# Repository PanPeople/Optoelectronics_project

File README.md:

# Optoelectronic Project

## Group Members:

* Mikołaj Czerniak
* Damian Kociołek
* Michał Stanisławski

## Useful links:

* https://www.electronics-lab.com/project/constant-current-laser-diode-driver-circuit-using-opa2350-opamp/
* https://www.electronics-lab.com/project/adjustable-constant-current-laser-diode-led-driver/
* https://github.com/marcoreps/laser_driver

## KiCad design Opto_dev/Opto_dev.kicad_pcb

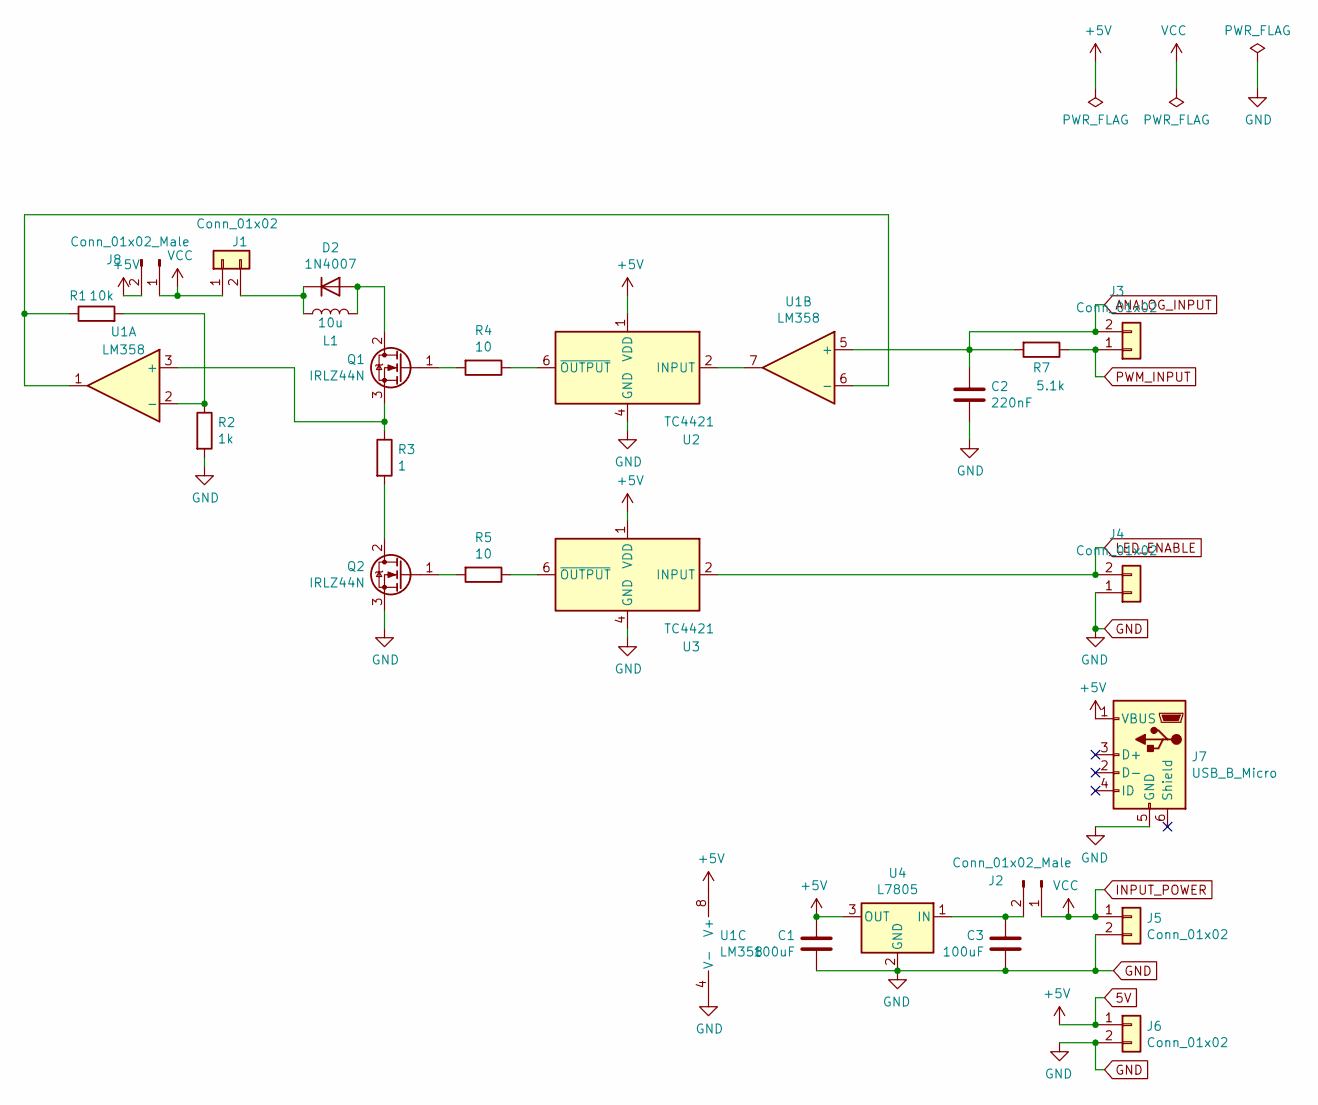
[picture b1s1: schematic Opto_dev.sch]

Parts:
C1, C3: 100uF; CP_Radial_D6.3mm_P2.50mm
C2: 220nF; C_Disc_D4.7mm_W2.5mm_P5.00mm
D2: 1N4007; D_DO-41_SOD81_P10.16mm_Horizontal
J1, J3, J4, J5, J6: Conn_01x02; TerminalBlock_bornier-2_P5.08mm
J2, J8: Conn_01x02_Male; PinHeader_1x02_P2.54mm_Vertical
J7: USB_B_Micro; PinHeader_1x05_P2.54mm_Vertical
L1: 10u; L_Radial_D9.5mm_P5.00mm_Fastron_07HVP
Q1, Q2: IRLZ44N; TO-220-3_Vertical
R1: 10k; R_Axial_DIN0204_L3.6mm_D1.6mm_P7.62mm_Horizontal
R2: 1k; R_Axial_DIN0204_L3.6mm_D1.6mm_P7.62mm_Horizontal
R3: 1; R_Axial_DIN0918_L18.0mm_D9.0mm_P22.86mm_Horizontal
R4, R5: 10; R_Axial_DIN0204_L3.6mm_D1.6mm_P7.62mm_Horizontal
R7: 5.1k; R_Axial_DIN0204_L3.6mm_D1.6mm_P7.62mm_Horizontal
U1: LM358; DIP-8_W7.62mm_Socket_LongPads
U2, U3: TC4421; DIP-8_W7.62mm_Socket_LongPads
U4: L7805; TO-220-3_Vertical

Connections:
5V: C1.1, J6.1, J7.1 (VBUS), J8.2, U1.8 (V+), U2.1 (VDD), U2.8 (VDD), U3.1 (VDD), U3.8 (VDD), U4.3 (OUT)
ANALOG_INPUT: C2.1, J3.2, R7.2, U1.5 (+)
GND: C1.2, C2.2, C3.2, J4.1, J5.2, J6.2, J7.5 (GND), Q2.3 (S), R2.2, U1.4 (V-), U2.4 (GND), U2.5 (GND), U3.4 (GND), U3.5 (GND), U4.2 (GND)
INPUT_POWER: J1.1, J2.1, J5.1, J8.1
LED_ENABLE: J4.2, U3.2 (INPUT)
unnamed: C3.1, J2.2, U4.1 (IN)
unnamed: D2.1 (K), J1.2, L1.1
unnamed: D2.2 (A), L1.2, Q1.2 (D)
unnamed: Q1.1 (G), R4.2
unnamed: Q1.3 (S), R3.1, U1.3 (+)
unnamed: Q2.1 (G), R5.2
unnamed: Q2.2 (D), R3.2
unnamed: R1.1, U1.1, U1.6 (-)
unnamed: R1.2, R2.1, U1.2 (-)
unnamed: R4.1, U2.6 (~OUTPUT), U2.7 (~OUTPUT)
unnamed: R5.1, U3.6 (~OUTPUT), U3.7 (~OUTPUT)
unnamed: U1.7, U2.2 (INPUT)
PWM_INPUT: J3.1, R7.1

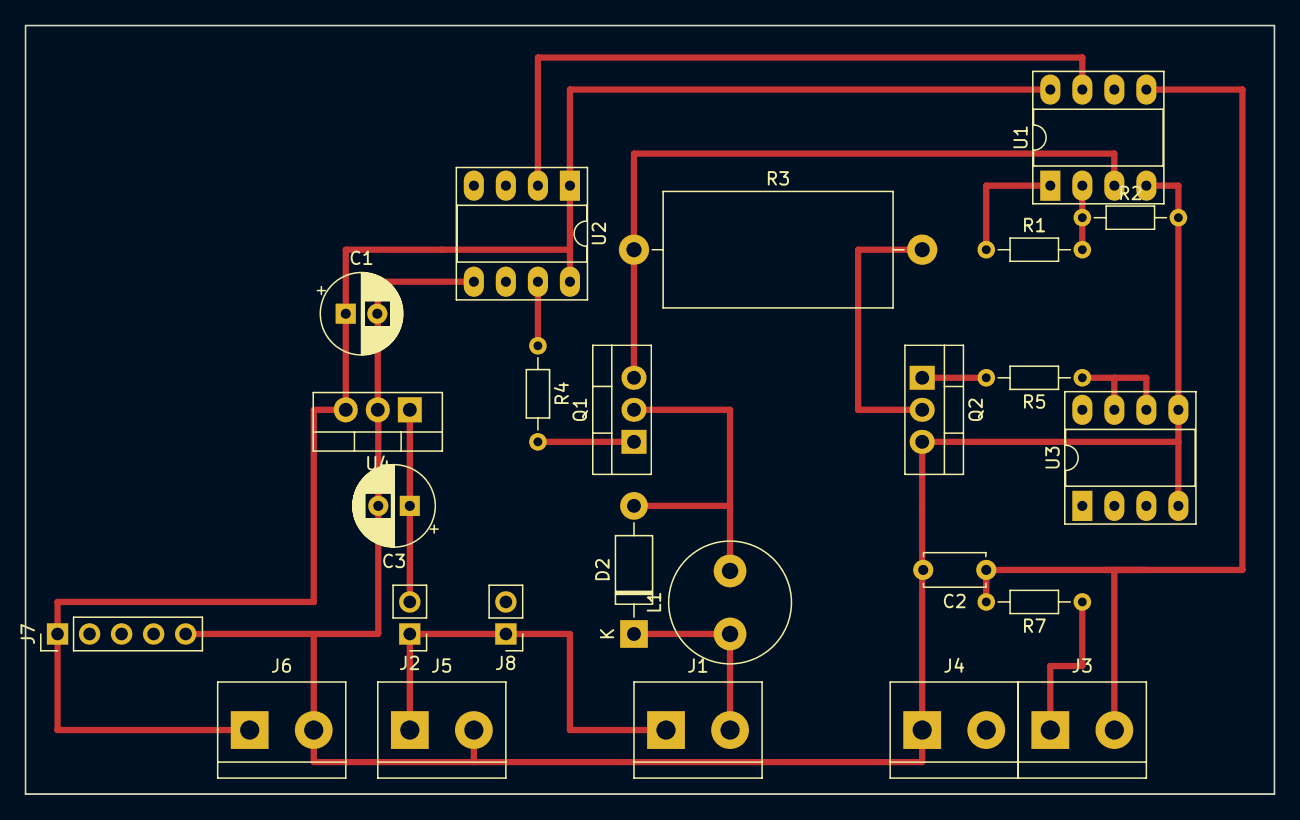
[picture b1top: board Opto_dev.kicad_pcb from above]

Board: 2 copper layers, 99.1 x 61.0 mm, 25 parts (0 on the bottom side), 18 nets.

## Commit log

2021-10-20 Added group members file
2021-10-20 rename file
2021-10-20 craate dev branch
2021-10-20 addet sefull tutorial
2021-10-28 Damian mnie bije xD
2021-11-18 Added schematics
2021-12-12 added code vith perfboard layout
2021-12-19 added code for uC and Python script
2022-01-16 updated python script
2022-01-30 minor changes
